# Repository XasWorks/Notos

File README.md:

# Notos

Public repository of the Notos robot project of the [Kolleg St. Thomas][kst] robotics group, competing in the 2016/2017 RoboCup Junior Line Secondary competition.

[kst]:http://www.kolleg-st-thomas.de

[![Autodesk Render][a360render]](http://a360.co/2o4hNXv)

[a360render]:Render.jpg

----------

# Features
Notos was built mainly with DIY-capability in mind. All components can be printed out with a home 3D printer of normal size, and can be easily bought or soldered at home. The total costs lay beneath 100€

- AVR-Based MCU (ATMega32 and ATMega328P)
- NEMA 14 stepper motors for both precision and power
- Completely 3D printed chassis with sturdy screw-connections
	- This even includes the belts themselves! (Flexible material printing capabilities required though)
- Completely open-source code and design, for everyone to work with
- Simple "stacking" design for sensor mounts, PCBs and other attachments, allowing for a great deal of flexibility.

# History
Notos was started in the late summer of 2016, by DIY-enthusiast David Bailey.
After his mildly successfull run with his first robot [Zephyr][zephyrRepo], awarding him the 20th place in the german-open championship in the RoboCup Line Secondary contest in 2016, he applied his newfound knowledge to build something more suitable for the contest.
As a name, it was only fitting to continue Zephyr's legacy by choosing another greek god of the wind: **Notos**

[zephyrRepo]:https://www.github.com/XasWorks/Hexa-Bot

# Development
To overcome the problems that the old robot Zephyr had, a lot of the elements had to be replaced, and a complete redesign was necessary. This design process began in the late summer of 2016, maintaining many of the features that made Zephyr successfull, while swapping out the bad parts. The AVR-MCU and stepper motor drive system had been kept, while chassis and omniwheel-design were traded in for a much sturdier and compacter design, as well as more reliable, self-printed belts.

As of now the development still continues, as only over time differet features, flaws, and ideas come apparent.

---

# Prerequisites
- Using the OpenSCAD models here requires having the [XasCode Library][XasCode] next to this (the Notos) repository, as the Tagging.scad function is used.
	Later on the AVR libraries of that repository will also be used, so it is recommended to clone it completely!
- To properly work with the AVR Code, it is recommended to install the [AVR-Plugin for eclipse][avrplug] (for C and C++ eclipse versions)
	The current workspace is in EclipseWS. Eclipse should auto-detect the projects, if not, use the "import C++ project" function and import the project folders inside EclipseWS

[avrplug]:http://avr-eclipse.sourceforge.net/wiki/index.php/The_AVR_Eclipse_Plugin
[XasCode]:https://www.github.com/XasWorks/XasCode

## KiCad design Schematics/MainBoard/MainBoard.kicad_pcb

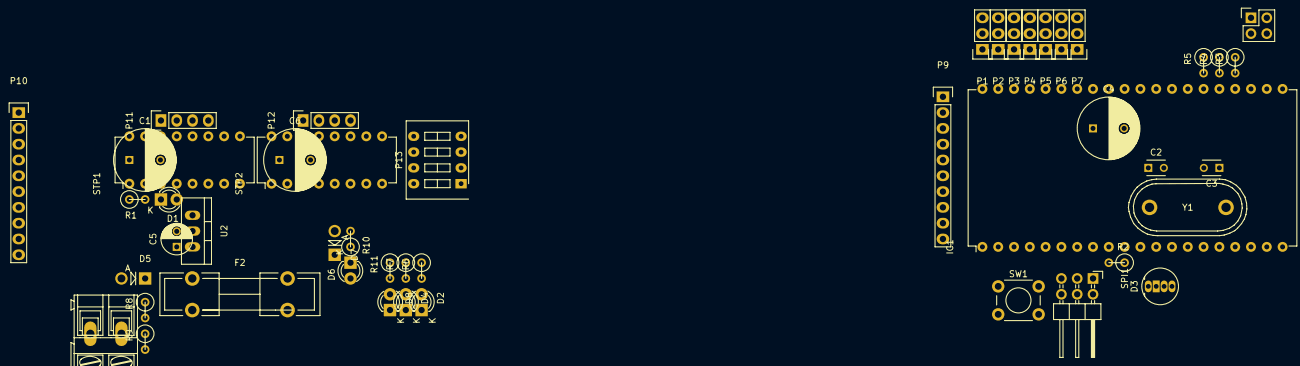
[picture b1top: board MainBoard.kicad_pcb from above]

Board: 2 copper layers, 47 parts (0 on the bottom side), 51 nets, no tracks yet.

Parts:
BT2: 4C LiPo; AK300-2
C1, C6: 220uF; C_Radial_D10_L16_P5
C2, C3: 56pF; C_Disc_D3_P2.5
C4: C_Small; C_Radial_D10_L16_P5
C5: 22uF; C_Radial_D5_L11_P2.5
D1, D2, D4, D6, D8: LED; LED-3MM
D3: LED_RCBG; LED-RGB-5MM_Common_Cathode
D5: D; Diode_DO-41_SOD81_Vertical_AnodeUp
D7: >6.8V; Diode_DO-41_SOD81_Vertical_AnodeUp
F2: 2A Fuse; Fuseholder5x20_horiz_open_lateral_Type-II
I2C1: CONN_02X02; Pin_Header_Straight_2x02
IC1: ATMEGA32-P; DIP-40_W25.4mm
P1, P2, P3, P4, P5, P6, P7: CONN_01X03; Pin_Header_Straight_1x03
P9, P10: CONN_01X10; Pin_Header_Straight_1x10
P11, P12: CONN_01X04; Pin_Header_Straight_1x04
P13: CONN_02X04; SW_DIP_x4_Slide
R1, R6, R7, R11: R; R1
R2: 5kΩ; R1
R3, R4, R5, R10: 1kΩ; R1
R8: 4.7kΩ; R1
R9: 2.2kΩ; R1
SPI1: CONN_02X03; Pin_Header_Angled_2x03
STP1, STP2: A4988; DIP-16_W7.62mm
SW1: SW_PUSH; SW_PUSH_6mm
U2: 5V Reg; TO-220_Neutral123_Vertical
Y1: 16MHz; Crystal_HC48-U_Vertical

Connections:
+5V: C4.1, I2C1.3, IC1.10, IC1.30, IC1.32, P1.2, P2.2, P3.2, P4.2, P5.2, P6.2, P7.2, P9.2, R2.1, SPI1.2
/BTN: IC1.5, SW1.1
/LEDB: IC1.26, R5.2
/LEDG: IC1.25, R4.2
/LEDR: IC1.24, R3.2
/MISO: IC1.7, SPI1.1
/MOSI: IC1.6, SPI1.4
/Power Supply/5V: C5.1, D1.2, D6.2, D7.1, P10.2, STP1.10, STP2.10
/Power Supply/12V: C1.1, C6.1, F2.2, R8.1, STP1.16, STP2.16
/Power Supply/MS1: P13.2, STP1.2, STP2.2
/Power Supply/MS2: P13.4, STP1.3, STP2.3
/Power Supply/MS3: P13.6, STP1.4, STP2.4
/RST: IC1.9, R2.2, SPI1.5
/SCK: IC1.8, SPI1.3
/SCL: I2C1.2, IC1.22
/SDA: I2C1.1, IC1.23
/SENS0: IC1.40, P1.1
/SENS1: IC1.39, P2.1
/SENS2: IC1.38, P3.1
/SENS3: IC1.37, P4.1
/SENS4: IC1.36, P5.1
/SENS5: IC1.35, P6.1
/SENS6: IC1.34, P7.1
/STEP0: IC1.1, P9.4, P10.4, R7.1, STP1.7
/STEP1: IC1.2, P9.5, P10.5, R11.1, STP2.7
/STEPD: IC1.3, P9.6, P10.6, R6.1, STP1.8, STP2.8
/STEPE: IC1.4, P9.7, P10.7, R1.1, STP1.1, STP2.1
/VSens: IC1.33, P9.3, P10.3, R8.2, R9.1
GND: BT2.2, C1.2, C2.2, C3.2, C4.2, C5.2, C6.2, D2.1, D3.2, D4.1, D7.2, D8.1, I2C1.4, IC1.11, IC1.31, P1.3, P2.3, P3.3, P4.3, P5.3, P6.3, P7.3, P9.1, P10.1, P13.1, P13.3, P13.5, R9.2, R10.2, SPI1.6, STP1.9, STP1.15, STP2.9, STP2.15, SW1.2
unnamed: BT2.1, D5.2
unnamed: C2.1, IC1.12, Y1.1
unnamed: C3.1, IC1.13, Y1.2
unnamed: D1.1, R1.2
unnamed: D2.2, R6.2
unnamed: D3.1, R5.1
unnamed: D3.3, R3.1
unnamed: D3.4, R4.1
unnamed: D4.2, R7.2
unnamed: D5.1, F2.1
unnamed: D6.1, R10.1
unnamed: D8.2, R11.2
unnamed: P11.1, STP1.14
unnamed: P11.2, STP1.13
unnamed: P11.3, STP1.12
unnamed: P11.4, STP1.11
unnamed: P12.1, STP2.14
unnamed: P12.2, STP2.13
unnamed: P12.3, STP2.12
unnamed: P12.4, STP2.11
unnamed: STP1.5, STP1.6
unnamed: STP2.5, STP2.6

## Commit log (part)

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2016-08-08 Started working on a first basic prototype model.
2016-08-08 Einführung einer Projekt-Übergreifenden Variablendatei für Konstanten.
2016-08-08 Hinzufügen des Motor-Modells zum Prototypen.
2016-08-08 Mehr Werte zu Values.scad hinzugefügt.
2016-08-08 Modell für Schrauben hinzugefügt.
2016-08-08 Naming-Convention-Änderung, sowie setzen von und in Values.scad
2016-08-09 K.A.
2016-08-09 Basisches 'Cut-Modell' für den Schrittmotor hinzugefügt.
2016-08-09 Datei für die Backplate-Werte hinzugefügt.
2016-08-09 Noch ein paar Kommentare hinzugefügt.
2016-08-10 Kleine Änderung an der README
2016-08-10 Hinzufügen eines ersten "offiziellen" Modelles einer Idler-Wheel Hälfte.
    Diese Hälfte soll später für die Aufhängung der Ketten verwendet werden, um sie in Platz zu halten.
2016-08-10 Sicherstellung dass das Kugellager auch immer in das Idler-Wheel reinpasst.
2016-08-10 Removed the # in there.
2016-08-11 Hinzufügen eines Modells für die Kette.
2016-08-11 Idler-Rad auf die Kette angepasst.
2016-08-11 Prototypendatei auf die neuen Motor-Räder und Idler umgestellt.
2016-08-11 Motor-Abstand war falsch berechnet worden.
2016-08-12 Modell für die Roboter-Backplate erstellt.
2016-08-12 Neues Backplate-Modell in die Prototypen-Form hinzugefügt.
2016-08-13 Zahn-Abstand so angepasst dass er sauber auf die Idler- und Motorräder passt.
2016-08-15 Umbenennung von BackplateTrackPlay zu plateTrackPlay.
2016-08-15 Einfügung der Platten-Verbindungselemente.
2016-08-15 Leichtes Code-Cleanup, closes #6
2016-08-16 Neue Frontplatte zum Modell hinzugefügt.
2016-08-16 Hardgecodeten Schrauben-Durchmesser durch Variable ersetzt.
2016-08-21 Anfang der Schematics eingefügt.
2016-08-21 Ungenutzte, leere Funktion entfernt
2016-08-21 Version 1.0 des Prototypen-Modells! (#7)
    * Modell für die Roboter-Backplate erstellt.
    * Langer Variablenname kleiner gemacht.
    * Neues Backplate-Modell in die Prototypen-Form hinzugefügt.
    * Zahn-Abstand so angepasst dass er sauber auf die Idler- und Motorräder passt.
    * Einfügung von Anbringungs-Stellen für zukünftige Module.
    * Umbenennung von BackplateTrackPlay zu plateTrackPlay.
2016-08-21 Erste Schritte zu einem Funktionalen Schaltplan.
2016-08-22 Schaltplan mit Beschreibungen erweitert und SPI angelegt.
2016-08-24 Erste Schritte für das Ketten-Längen-Berechnungs-Skript.
2016-08-25 Zusammenführung zweier Funktionen in eine Gesamtfunktion\n Dise kann nun sowohl Tangenten-Länge als auch Winkel bestimmen.
2016-09-05 Debug-Nachrichten zum Track Cal hinzugefügt.
2016-09-05 Neue Datei für einen Perl-Compiler angelegt!
2016-09-10 Endlich herausgefunden wie 'use' geht ...
2016-09-11 Option für fest eingestellte Zahn-Anzahl hinzugefügt.
2016-09-12 Motor-Wheel wieder auf 15mm gesetzt
    Remnant aus dem Debugging-Branch, sorry.
2016-09-14 Winkel der 'Front' der Kette auf 45° gesetzt.
2016-09-15 Überspannungsdiode, I2C, Sicherung hinzugefügt.
2016-09-17 EXPORT_OK geupdated.
2016-09-17 Design umgeändert auf Nutless design. Closes #11 (Sollte es zumindest).
    Geändert wurden hauptsächlich:
    - Frontplate
    - Backplate
    - idlerwheel_screw
    Die Änderung in Motorwheel.scad ist ein bug, entstanden durch die Änderung von Track.scad
2016-09-20 Hinzufügung des basischen Filetree-Systemes
    Momentan kann der File-Tree eines gegebenen Code-Systemens mithilfe von MKDIR in einem Ordner (default ./BIN) erstellt werden.
    Man sollte jedoch vielleicht noch ein paar Fehler abfangen, wie z.B. nicht existierende Dateien etc.
    Mal schauen.
2016-09-21 Scematic-Layout für den A4988 Treiber eingebaut.
2016-09-22 Beendung des Umänderns des Platinen-Designs. Das neue System beinhaltet nun: - Alle für den Roboter relevanten Bauteile (inclusive A4988 Treiber) - Erweiterte Dokumentation des Schaltkreises - Ein se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
2016-09-23 S. vorheriger, ausversehener Commit ...
2016-09-24 Redesign der Idler_Screws für #16
    Das Redesign:
    - sorgt dafür, dass die Schrauben an der richtigen Position sitzen (Anfang des Schraub-Schaftes am Anfang der BP),
    - räumt ein wenig auf und
    - Fügt den Fix für den einfachereren Druck (config wert idlerScrewHeadSlope) hinzu.
2016-09-24 Halbierung des Idlerwheels für leichteres Drucken
2016-09-26 Plate connectors für #19 verändert.
    Jetzt sind auch die jeweiligen "Connectoren" verfügbar. Yay!
2016-09-26 Wertejustierungen für #20 Hauptsächlich sind die Werte der Größen für den Schrauben-Kopf und -Shaft verändert worden, um alles etwas besser zusammen zu halten.
2016-09-26 Globales zur Verfügung stellen von Tagging.scad
2016-09-26 IdlerTest.scad für Idler-Tests eingefügt
2016-09-27 Positionsänderung des TagSystem auf XasCode
2016-09-27 Idler auf TagSystem umgestellt.
2016-09-27 Tagging von ModuleMount.scad
2016-09-27 Tagging der Frontplate
2016-09-28 Entfernung einiger Überbleibsel
2016-09-28 Entfernung des use aus Tools.scad - Geht eh nicht
2016-09-29 Hinzufügung eines lagerlosen Idlerwheel
    Es sollte sich in einem Stück drucken lassen, und auch ohne Bearings sehr reibungsarm laufen können!
    ---
    Zudem wurde auch noch smallWheelSize zu idlerwheelSize umbenannt, um alles etwas konsistenter zu halten!
2016-09-29 Hinzufügen eines ersten Verbinder-Blocks
2016-09-29 TrackSetup um Adapterplatten erweitert
    UNGLAUBLICH Sorry für den accidental merge mit master.
    *seufz*
    Mein Fehler.
2016-09-29 Leichte Modifikation der modulesPositions
2016-10-05 Symlink zu XasCode Bibliothek.
2016-10-07 Footprints der Teile hinzugefügt.
2016-10-07 Anfänge des Designs des PCB
2016-10-08 Schaltplan-Additionen für die neuen LEDs
2016-10-09 Anpassungen an die echten Schaltkreise
2016-10-15 Einbindung der TIMER und STEPPER Bibliotheken :D
2016-10-15 Automatische Spannungsmessung hinzugefügt.
2016-10-18 Implementation of new ADC Ref selection
2016-10-22 Justierung der Schaltplan für #27
2016-10-22 Zurücksetzen des VRef auf extern. Vcc
2016-10-24 Anpassung für die neue ISRStepAllBy()
2016-10-25 Spielereien mit dem neuen X2::Movable
2016-10-31 Kleine Spielerei mit dem Code :D
2016-10-31 Spielereien mit dem neuen LF::Sens3
2016-10-31 Umbewegung vieler System-Funktionen in Robot.h
2016-11-05 Einbindung eines Battery-Guards
2016-11-06 Anpassungen an das gedruckte Modell sowie neue StatusLED
2016-11-08 Kleine Änderung für besseren Halt
2016-11-09 Einfügung eines Prototypen-Modul-Verbinders
2016-11-10 Hinzufügen eines ordentlichen, stabilen Verbinders!
2016-11-12 Kleine Änderungen für Passgenauigkeit.
2016-11-12 Pretty Pretty Logo
2016-11-12 Hinzufügen eines Griffes
2016-11-14 Hinzufügen eines Plating-Spacers
2016-11-18 Nutzung eines für OpenSCAD schnelleren STL-Import
2016-11-18 Neue Datei für die LF-Module
2016-11-22 Hinzufügen eines Spacers für die Elektronik
2016-11-26 Modifizierung der LF-Halterung für #34
2016-12-08 Kleines unnötiges # entfernt
2016-12-08 Hinzufügen eines Logo-Stempels, closes #3
    Sowie: Leichte Änderung für schnelles Drucken
2016-12-08 Säuberung für PR #35
    - Entfernung von check_voltage, für #35
    - Hinzufügen von ISR_LED_FREQ, #35
    - Kleines unnötiges # entfernt
2016-12-13 LFShield angepasst - #37
2016-12-13 Positionsanpassung für #37
2016-12-14 Hinzufügen eines LF-Skelets
2016-12-14 Mehr User-Interface-Optionen!
2016-12-14 Enum für Init-Status
2017-01-07 Änderungen für PR #38
2017-01-07 enableCTC jetzt mit Macro
2017-01-25 Added a 'stateFunction' function pointer & USB state.
2017-01-27 Added object avoidance code!
2017-01-28 Add Codacy badge
2017-02-03 [Finally properly used Pins.h]
2017-02-03 Fix for #43, small fixes for #39
2017-02-04 Added mounting models for Line and Ground-Sensors
2017-02-05 Began rework of PerlC For now: Restructuring of the different files, using new package knowledge :D
2017-02-05 Added a $workEnv variable for data storage
2017-02-10 Speed-Adjustments
2017-02-11 Small works on the PerlC. WILL BE DISCARDED!
2017-02-13 Buffer-Wert für graduelle Speed-Änderung
2017-02-13 Klammer vergessen >.>
2017-02-13 Return to a instantaneous system
2017-02-13 You obviously need rotation >.>
2017-02-14 {Etwas bessere Doku, und Auftrennung des Codes.}
2017-02-15 Speed changes!
2017-02-16 {New Mount for the Greyscale Sensor!
2017-02-18 Debug-Coding for intsec detection.
2017-02-20 Adjustment of how the intsec is scanned
2017-02-21 Small refinements for #48
2017-02-21 Intersection Implementation!! (#48)
    * {Etwas bessere Doku, und Auftrennung des Codes.}
    * Speed changes!
    * Modification for the new PIND array
    * Debug-Coding for intsec detection.
    * Implementation of first working INTSEC code!
    * Adjustment of how the intsec is scanned
2017-02-22 Value changes form Testing
2017-03-09 Added capability to change object avoid direction.
2017-03-09 Improvements to bump/ramp avoidance & buttonPause
2017-03-09 Changed some parameters of Intersection detection
2017-03-09 Changed startup behavior to autostart w.o. button
2017-03-09 Gitignore addition
2017-03-13 Implementation of a circle-based avoid code
2017-03-15 DO. NOT. DELETE. CPROJECT
2017-03-22 Start of the peripherals module design!
2017-03-25 Value adjustments
2017-03-25 Added a side-mounted laser attachment
2017-03-27 {New models for a LRP and the distance, bumper & laser sensor}
2017-03-30 Made the laser mount smaller
2017-04-04 Apparently, wasn't saved correcty!
2017-04-04 Addition of variable pull-down for A0
2017-04-04 Improved models to hold both laser and phototransistor!
2017-04-10 Added laser-timeout & Ball Detect Thresholds
    More precisely:
    After receiving a TWI signal, the laser will be on for ~2.5 seconds, measuring constantly.
    Additionally, it will not "flicker" between "Ball" and "No Ball",
    instead it has a Schmidt-Trigger like setup to make readings more consistent.
2017-04-10 Added Packets.h This file is there to give one single, always-matching definition for both structs, as well as one Enum governing the communication commands.
2017-04-10 Added the TWI System & PeripheralsModule Job class
2017-04-10 Ball Laser now USB-Debugged & test Ball search
2017-04-10 Changed to Arduino Programmer for now
2017-04-10 Mods for the PR
2017-04-10 Laser & Peripherals Module! (#51)
    * DO. NOT. DELETE. CPROJECT
    * Added new prototyping model to mount a laser & greyscale.
    * Start of the peripherals module design!
    * Adjusted the mount for 12mm laser
    * Value adjustments
    * Added a side-mounted laser attachment
2017-04-11 Maser-Side configurable Threshold
2017-04-11 Added a SET_THRESHOLD command
2017-04-16 Changed microstepping back to 8
2017-04-20 New Models for the ball search!
2017-04-20 Slave-Side servo control class
2017-04-20 First test code for the ball search
2017-04-20 Actual implementation of new servo class
2017-04-20 Fixes for PR #52
2017-04-20 Fix to have "Notos" still a header
2017-04-23 Ensured a "0"-hitStatus when restarting laser
2017-04-23 Adjustments for ballSearch testing
2017-04-23 Configuration for BallBoop & Conductance sensor
2017-04-23 Added hooks for the BallSearch
2017-04-23 Programmer CFG change ... ?
2017-04-25 Modified servo motor state change speed
2017-04-25 Complex ... Lots of stuff.
2017-04-26 Small adjustments to the cap process
2017-04-27 Fixed rotation, better drop detection & self-alignment
2017-04-27 Ensured a 1mW laser (20% duty cycle)
2017-04-28 Pretty nice redesign of README
2017-04-28 Trying to get the Autodesk model viewer to work D:
2017-04-28 Added a nice, linked Autodesk render
2017-05-01 Added a card holder for the contact cards
2017-05-02 Modified greyscale mount for less false-triggers
2017-05-02 Removed picture URL (It changes D:)
2017-05-02 Removed .cproject and .project from being `diff`ed
2017-05-02 Fixed the "Robot does not return" bug
